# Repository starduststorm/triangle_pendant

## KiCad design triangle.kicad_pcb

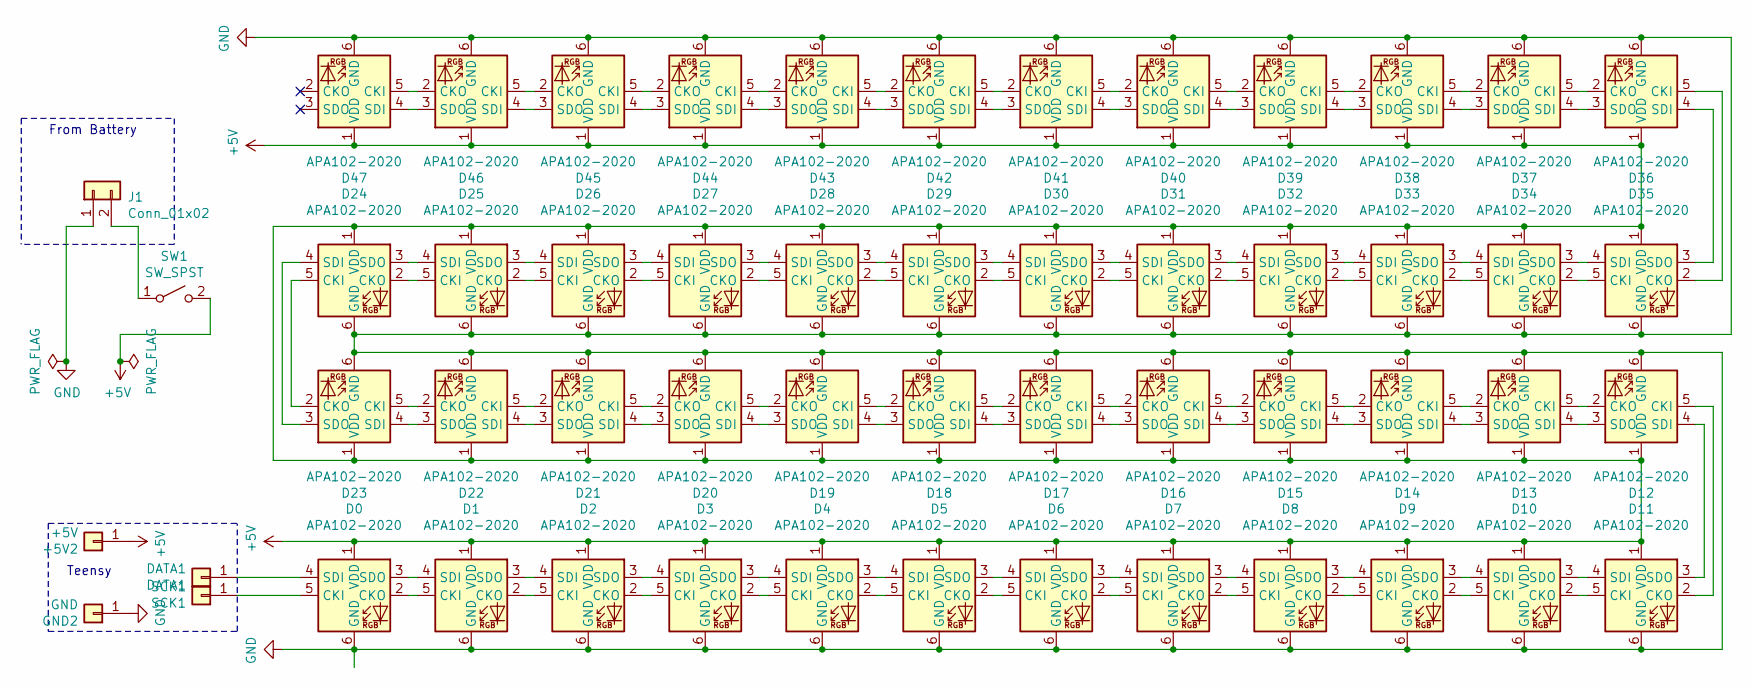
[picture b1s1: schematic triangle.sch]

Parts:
+5V2: +5V; PinHeader_1x01_P2.54mm_Vertical
D0, D1, D2, D3, D4, D5, D6, D7, D8, D9, D10, D11, D12, D13, D14, D15, D16, D17, D18, D19, D20, D21, D22, D23, D24, D25, D26, D27, D28, D29, D30, D31, D32, D33, D34, D35, D36, D37, D38, D39, D40, D41, D42, D43, D44, D45, D46, D47: APA102-2020; LED-APA102-2020
DATA1: DATA1; PinHeader_1x01_P2.54mm_Vertical
GND2: GND; PinHeader_1x01_P2.54mm_Vertical
J1: Conn_01x02; PinHeader_1x02_P2.54mm_Vertical
SCK1: SCK1; PinHeader_1x01_P2.54mm_Vertical
SW1: SW_SPST; SW_SPDT_PCM12

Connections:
unnamed: D0.2 (CKO), D1.5 (CKI)
unnamed: D0.3 (SDO), D1.4 (SDI)
unnamed 2: D0.4 (SDI), DATA1.1; also elsewhere on the board
unnamed 3: D0.5 (CKI), SCK1.1; also elsewhere on the board
unnamed: D1.2 (CKO), D2.5 (CKI)
unnamed: D1.3 (SDO), D2.4 (SDI)
unnamed: D2.2 (CKO), D3.5 (CKI)
unnamed: D2.3 (SDO), D3.4 (SDI)
unnamed: D3.2 (CKO), D4.5 (CKI)
unnamed: D3.3 (SDO), D4.4 (SDI)
unnamed: D4.2 (CKO), D5.5 (CKI)
unnamed: D4.3 (SDO), D5.4 (SDI)
unnamed: D5.2 (CKO), D6.5 (CKI)
unnamed: D5.3 (SDO), D6.4 (SDI)
unnamed: D6.2 (CKO), D7.5 (CKI)
unnamed: D6.3 (SDO), D7.4 (SDI)
unnamed: D7.2 (CKO), D8.5 (CKI)
unnamed: D7.3 (SDO), D8.4 (SDI)
unnamed: D8.2 (CKO), D9.5 (CKI)
unnamed: D8.3 (SDO), D9.4 (SDI)
unnamed: D10.2 (CKO), D11.5 (CKI)
unnamed: D10.3 (SDO), D11.4 (SDI)
unnamed: D9.3 (SDO), D10.4 (SDI)
unnamed: D9.2 (CKO), D10.5 (CKI)
unnamed: D11.2 (CKO), D12.5 (CKI)
unnamed: D11.3 (SDO), D12.4 (SDI)
unnamed: D12.2 (CKO), D13.5 (CKI)
unnamed: D12.3 (SDO), D13.4 (SDI)
unnamed: D13.2 (CKO), D14.5 (CKI)
unnamed: D13.3 (SDO), D14.4 (SDI)
unnamed: D14.2 (CKO), D15.5 (CKI)
unnamed: D14.3 (SDO), D15.4 (SDI)
unnamed: D15.2 (CKO), D16.5 (CKI)
unnamed: D15.3 (SDO), D16.4 (SDI)
unnamed: D16.2 (CKO), D17.5 (CKI)
unnamed: D16.3 (SDO), D17.4 (SDI)
unnamed: D17.2 (CKO), D18.5 (CKI)
unnamed: D17.3 (SDO), D18.4 (SDI)
unnamed: D18.2 (CKO), D19.5 (CKI)
unnamed: D18.3 (SDO), D19.4 (SDI)
unnamed: D19.2 (CKO), D20.5 (CKI)
unnamed: D19.3 (SDO), D20.4 (SDI)
unnamed: D20.2 (CKO), D21.5 (CKI)
unnamed: D20.3 (SDO), D21.4 (SDI)
unnamed: D21.2 (CKO), D22.5 (CKI)
unnamed: D21.3 (SDO), D22.4 (SDI)
unnamed: D22.2 (CKO), D23.5 (CKI)
unnamed: D22.3 (SDO), D23.4 (SDI)
unnamed: D23.2 (CKO), D24.5 (CKI)
unnamed: D23.3 (SDO), D24.4 (SDI)
unnamed: D24.2 (CKO), D25.5 (CKI)
unnamed: D24.3 (SDO), D25.4 (SDI)
unnamed: D25.2 (CKO), D26.5 (CKI)
unnamed: D25.3 (SDO), D26.4 (SDI)
unnamed: D26.2 (CKO), D27.5 (CKI)
unnamed: D26.3 (SDO), D27.4 (SDI)
unnamed: D27.2 (CKO), D28.5 (CKI)
unnamed: D27.3 (SDO), D28.4 (SDI)
unnamed: D28.2 (CKO), D29.5 (CKI)
unnamed: D28.3 (SDO), D29.4 (SDI)
unnamed: D29.2 (CKO), D30.5 (CKI)
unnamed: D29.3 (SDO), D30.4 (SDI)
unnamed: D30.2 (CKO), D31.5 (CKI)
unnamed: D30.3 (SDO), D31.4 (SDI)
unnamed: D31.2 (CKO), D32.5 (CKI)
unnamed: D31.3 (SDO), D32.4 (SDI)
unnamed: D32.2 (CKO), D33.5 (CKI)
unnamed: D32.3 (SDO), D33.4 (SDI)
unnamed: D33.2 (CKO), D34.5 (CKI)
unnamed: D33.3 (SDO), D34.4 (SDI)
unnamed: D34.2 (CKO), D35.5 (CKI)
unnamed: D34.3 (SDO), D35.4 (SDI)
unnamed: D35.2 (CKO), D36.5 (CKI)
unnamed: D35.3 (SDO), D36.4 (SDI)
unnamed: D36.2 (CKO), D37.5 (CKI)
unnamed: D36.3 (SDO), D37.4 (SDI)
unnamed: D37.2 (CKO), D38.5 (CKI)
unnamed: D37.3 (SDO), D38.4 (SDI)
unnamed: D38.2 (CKO), D39.5 (CKI)
unnamed: D38.3 (SDO), D39.4 (SDI)
unnamed: D39.2 (CKO), D40.5 (CKI)
unnamed: D39.3 (SDO), D40.4 (SDI)
unnamed: D40.2 (CKO), D41.5 (CKI)
unnamed: D40.3 (SDO), D41.4 (SDI)
unnamed: D41.2 (CKO), D42.5 (CKI)
unnamed: D41.3 (SDO), D42.4 (SDI)
unnamed: D42.2 (CKO), D43.5 (CKI)
unnamed: D42.3 (SDO), D43.4 (SDI)
unnamed: D43.2 (CKO), D44.5 (CKI)
unnamed: D43.3 (SDO), D44.4 (SDI)
unnamed: D44.2 (CKO), D45.5 (CKI)
unnamed: D44.3 (SDO), D45.4 (SDI)
unnamed: D45.2 (CKO), D46.5 (CKI)
unnamed: D45.3 (SDO), D46.4 (SDI)
unnamed: D46.2 (CKO), D47.5 (CKI)
unnamed: D46.3 (SDO), D47.4 (SDI)

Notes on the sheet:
Teensy
From Battery

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
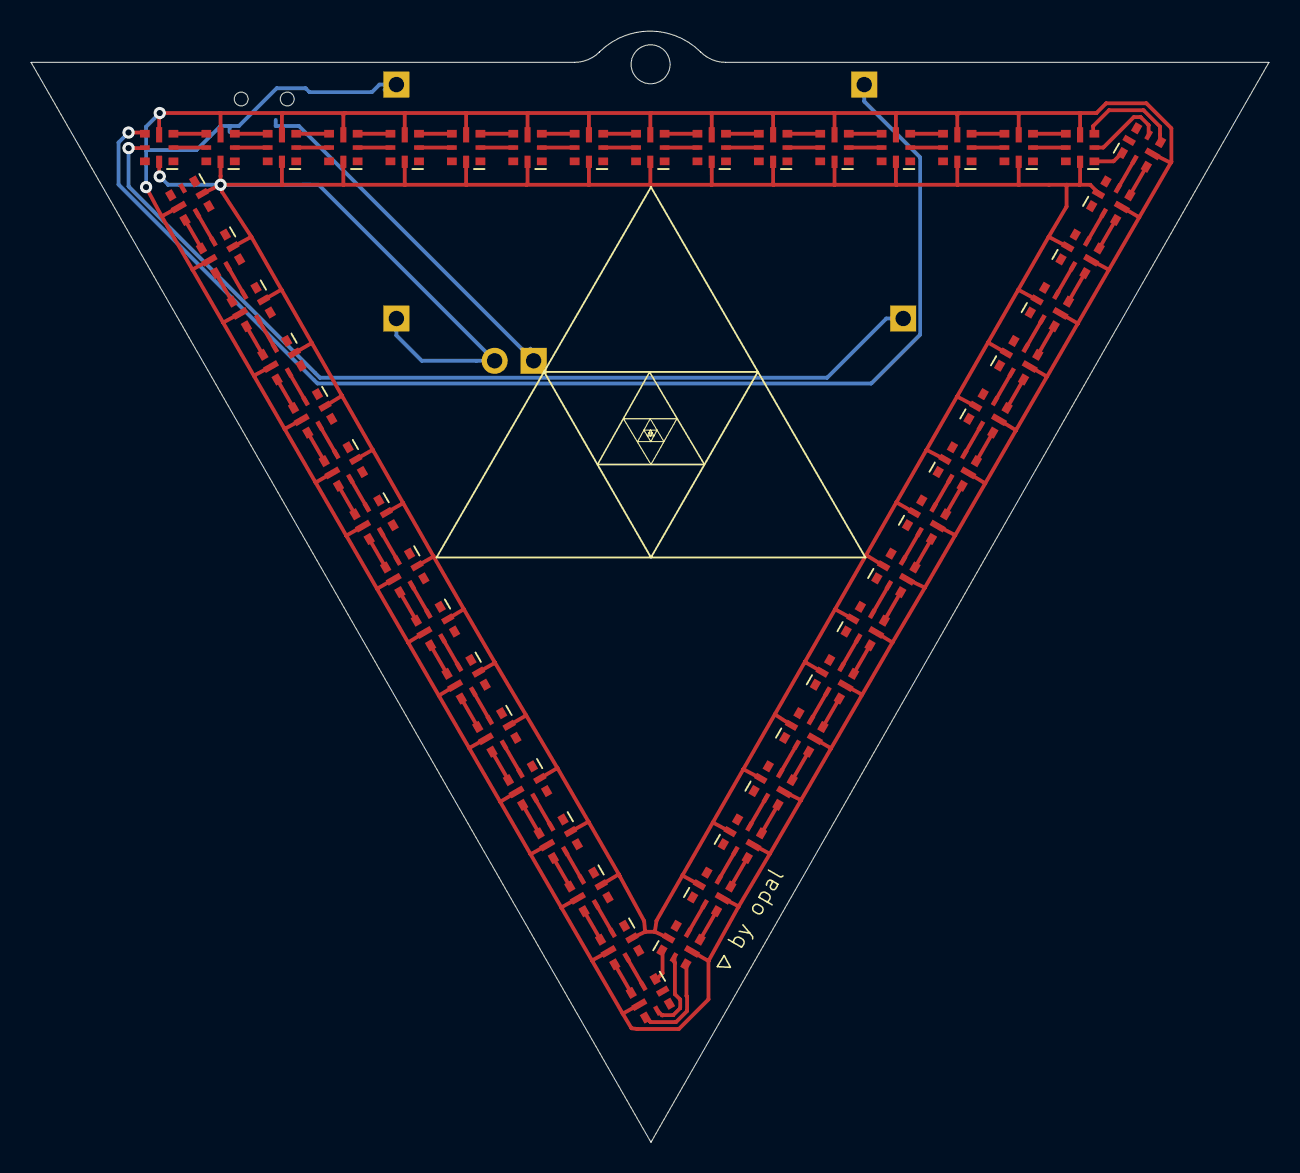
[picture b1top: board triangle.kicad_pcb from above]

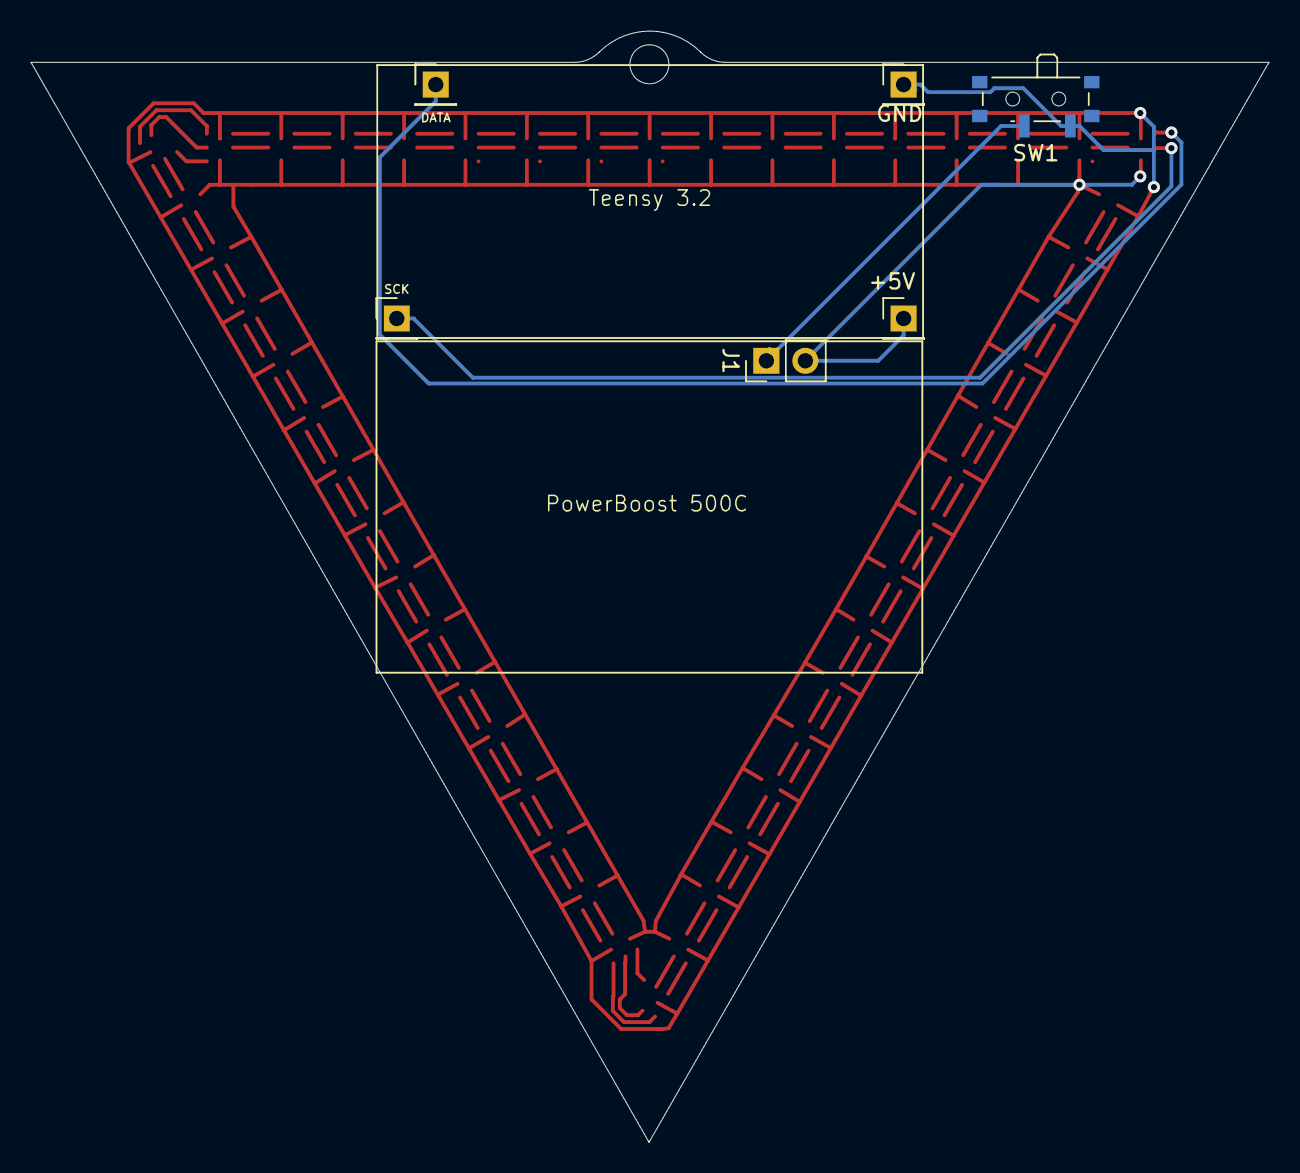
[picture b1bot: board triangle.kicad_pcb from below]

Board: 2 copper layers, 80.6 x 72.4 mm, 54 parts (6 on the bottom side), 98 nets.

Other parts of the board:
+5V: +5V; PinHeader_1x01_P2.54mm_Vertical
DATA: DATA1; PinHeader_1x01_P2.54mm_Vertical
GND: GND; PinHeader_1x01_P2.54mm_Vertical
SCK: SCK1; PinHeader_1x01_P2.54mm_Vertical

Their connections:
unnamed 2: DATA.1; also elsewhere on the board
unnamed 3: SCK.1; also elsewhere on the board

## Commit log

2019-07-30 initial commit of triangle wearable board
2019-07-30 remove TODO label
2019-07-30 add .gitignore
2019-07-30 add a cutout at the top center for pendant hanging
2019-07-30 tweaks to edge cuts and traces for symmetry
2019-07-31 remove some more zero-length traces
2019-07-31 hide led numbers; scoot boards over to minimize overhang
2019-07-31 sign it
2019-07-31 add decoration
2019-08-15 commit a change left in working directory, not sure what changed
2019-08-15 commit the fucking 5v lines to the corner leds...
2020-02-11 (committing old change) tighten APA102-2020 pad spacing to make it easier (read: possible) to solder
2020-02-11 drop in modified code from i am a ∆ to bootstrap small-triangle code
2020-07-12 rework/cleanup to make triangle pendant more of a pride-pink-triangle wearable
2025-06-22 build fixes
